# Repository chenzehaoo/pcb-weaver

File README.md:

# PCB Weaver

面向 PCB 工程的本机 MCP 与工作台：以 KiCad 为主链路，另提供独立的 Altium 静态检查内测服务。

> [!IMPORTANT]
> 项目处于开发者内测阶段。**KiCad 的样例验收不等于任意 PCB 都能自动布通；Altium 服务目前不能自动布线或回写 PCB。** 软件检查也不能替代工程师审查、打样与制造签核。

## 能力概览

| 入口 | 已实现 | 尚未覆盖 |
| --- | --- | --- |
| **KiCad 主 MCP** | 工程导入、约束布局、布线编排、原生复验、ECO、受门禁保护的制造包 | 任意复杂板的全自动完成；硬件可靠性和量产签核 |
| **Altium 内测 MCP** | 允许目录内的静态工程检查、持久任务、断线续查 | 自动布线、PCB 回写、完整 DRC、制造放行 |

## 为什么做

让 AI 参与 PCB 设计，需要让它读取真实工程、调用本机工具，并把修改结果交回设计软件检查。PCB Weaver 将这些操作组织成有版本、有任务记录、有原生证据的工程流程。

输入是**已有原理图、网络和封装的 KiCad 工程，以及结构化约束**。项目可以用于梳理工程信息、比较受约束的布局候选、提交布线与有限修复任务、检查修改结果和追踪版本变化。

## 系统架构

**图 1｜系统分层与工程域边界。** AI 客户端通过 MCP 调用工具；工作台提供本机 HTTP 入口。持久任务由工作台线程或独立 Worker 执行，KiCad 工程服务管理约束、版本和发布门禁。Altium 使用自己的 MCP、任务库与 Worker，默认仅运行静态检查。点击图片可查看矢量原图。

### KiCad 主链路如何工作

1. **导入工程**：复制工程文件与约束，记录文件哈希，建立版本快照。
2. **计算布局**：根据固定器件、区域、邻近和间距等约束生成候选，应用可行候选后创建子版本。
3. **调用布线工具**：KiCad/pcbnew 导出 DSN，Freerouting 生成 SES，再回导为待验证版本。
4. **原生复验**：运行对应版本的 ERC/DRC、网表一致性与几何等检查，保存具体失败原因和证据。
5. **显式发布**：请求制造包时重新检查，再导出真实产物、记录清单与归档哈希。

布局候选可行、布线回导成功、作业完成和制造门禁通过是不同结论。完整的[技术架构](docs/ARCHITECTURE.zh-CN.md)包含五张图，进一步说明模块分工、有限修复、版本证据、执行模型和 Altium 边界。

## 快速开始

**KiCad 主链路**（Windows PowerShell）：

```powershell
./Setup.ps1
./Start-Platform.ps1
```

需先准备 Python 3.11+。工作台默认在 `http://127.0.0.1:8765`；端口占用时运行 `./Start-Platform.ps1 -Port 8766`。`Setup.ps1` 安装项目 Python 依赖并生成本机 `.mcp.json`；原生路由仍需另行安装 KiCad、Java 和 Freerouting，并核对 `toolchain.unified.json` 的 WSL 与工具路径配置。

将 `.mcp.json` 中完整的 `pcb-weaver` 条目按客户端要求导入，启用并重载。工作台默认承载队列执行；也可以运行 `./Start-Worker.ps1` 单独执行任务。**仅连接 MCP 不会启动队列 Worker**。工作台 URL 不是 MCP stdio 地址。

完整步骤与故障排查见[部署与 MCP 接入](docs/GETTING-STARTED.zh-CN.md)。可用 `./Run-Demo.ps1` 运行小板回归，`-Route` 才会尝试完整工具链。

**Altium 静态检查内测**（单独配置）：

```powershell
./Setup-Altium-Service.ps1 -ProjectRoot 'D:\PCB-Projects'
./Start-Altium-Service.ps1
```

把生成的 `altium-local-developer-beta` 条目添加到支持 stdio 的 MCP 客户端。先调用 `altium_service_status`，再提交 `altium_submit_inspection`；任务结果用 `altium_get_job` 查询。完整安装及限制见[内测配置](docs/GITHUB-RELEASE.zh-CN.md)。

## 文档导航

| 想了解 | 文档 |
| --- | --- |
| 从安装到 MCP 调用与后台执行 | [部署与 MCP 接入](docs/GETTING-STARTED.zh-CN.md) |
| 模块、任务、版本和工程门禁 | [技术架构](docs/ARCHITECTURE.zh-CN.md) |
| Altium 工具与故障恢复 | [Altium 内测服务](docs/ALTIUM-SERVICE-BETA.zh-CN.md) |
| 本机机器接口与企业接入边界 | [集成说明](docs/INTEGRATION.zh-CN.md) |
| KiCad 实测范围与历史记录 | [固定布局验收](docs/FIXED-WHOLEBOARD-VALIDATION.md)、[系统验证](docs/SYSTEM_VALIDATION.zh-CN.md) |
| 完整文档目录与图源 | [文档导航](docs/README.md)、[架构图维护](docs/assets/architecture/README.md) |

公开仓库不包含本机工程、配置和大体积原生验收存档；克隆后必须在自己的工具链上重新验证。主项目使用 [Apache-2.0](LICENSE)，示例与第三方材料按[各自许可](THIRD_PARTY.md)使用。

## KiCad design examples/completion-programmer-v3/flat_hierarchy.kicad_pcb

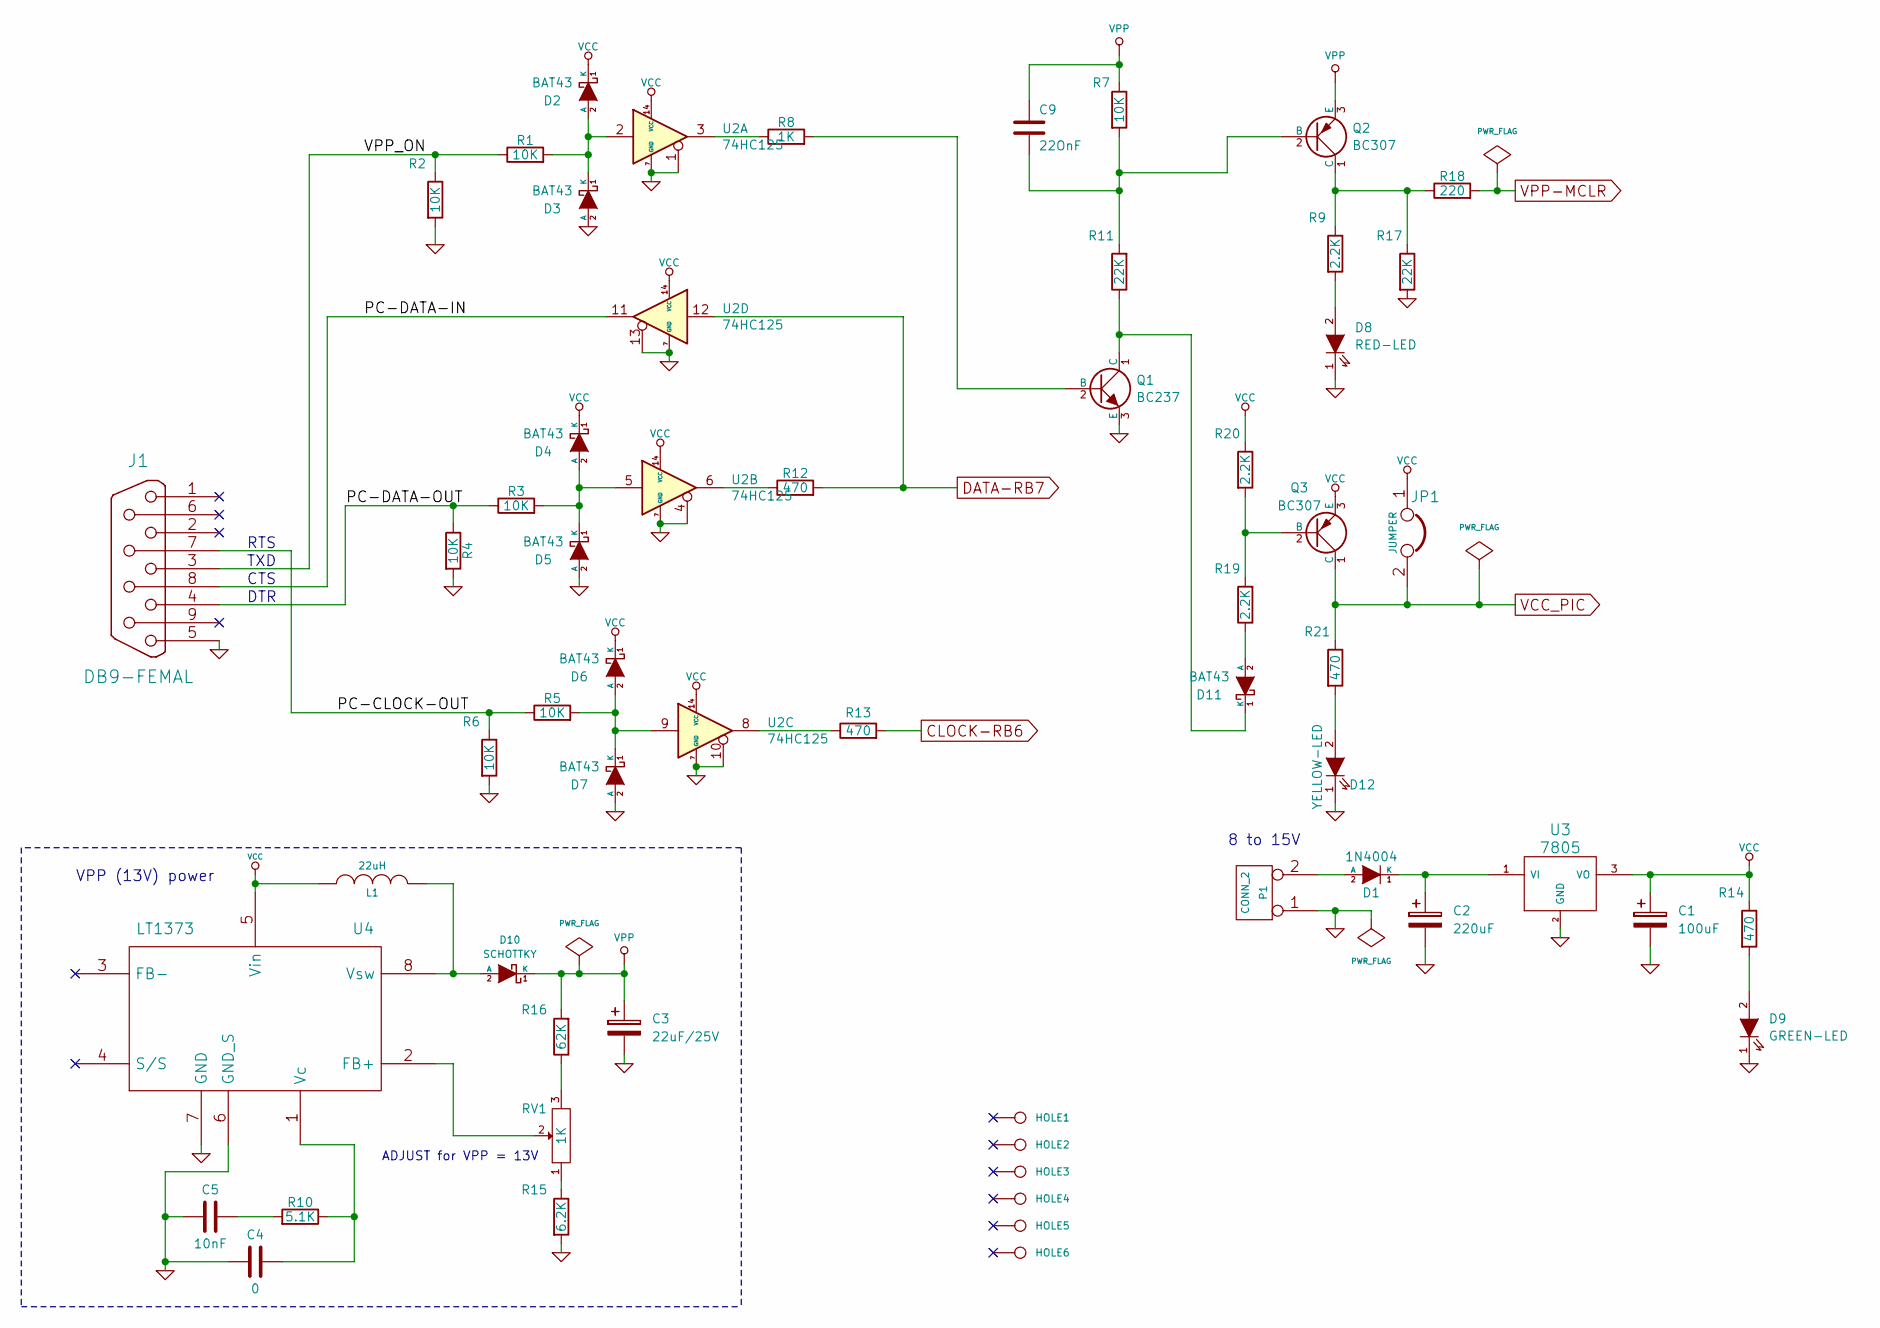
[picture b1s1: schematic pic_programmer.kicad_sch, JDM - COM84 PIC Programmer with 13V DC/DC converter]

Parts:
C1: 100uF; CP_Axial_L18.0mm_D6.5mm_P25.00mm_Horizontal
C2: 220uF; CP_Axial_L18.0mm_D6.5mm_P25.00mm_Horizontal
C3: 22uF/25V; CP_Axial_L11.0mm_D6.0mm_P18.00mm_Horizontal
C4: 0; C_Disc_D5.1mm_W3.2mm_P5.00mm
C5: 10nF; C_Disc_D5.1mm_W3.2mm_P5.00mm
C9: 22OnF; C_Disc_D5.1mm_W3.2mm_P5.00mm
D1: 1N4004; D_DO-35_SOD27_P12.70mm_Horizontal
D2, D3, D4, D5, D6, D7, D11: BAT43; D_DO-35_SOD27_P7.62mm_Horizontal
D8: RED-LED; LED_D5.0mm
D9: GREEN-LED; LED_D5.0mm
D10: SCHOTTKY; D_DO-35_SOD27_P12.70mm_Horizontal
D12: YELLOW-LED; LED_D5.0mm
HOLE1, HOLE2, HOLE3, HOLE4, HOLE5, HOLE6: P***; MountingHole_4.3mm_M4_DIN965
J1: DB9-FEMAL; DSUB-9_Female_Horizontal_P2.77x2.84mm_EdgePinOffset7.70mm_H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
JP1: JUMPER; PinHeader_1x02_P2.54mm_Vertical
L1: 22uH; INDUCTOR_V
P1: CONN_2; Altech_AK300_1x02_P5.00mm_45-Degree
Q1: BC237; TO-92
Q2, Q3: BC307; TO-92
R1, R2, R3, R4, R5, R6, R7: 10K; R_Axial_DIN0207_L6.3mm_D2.5mm_P10.16mm_Horizontal
R8: 1K; R_Axial_DIN0207_L6.3mm_D2.5mm_P10.16mm_Horizontal
R9, R19, R20: 2.2K; R_Axial_DIN0207_L6.3mm_D2.5mm_P10.16mm_Horizontal
R10: 5.1K; R_Axial_DIN0207_L6.3mm_D2.5mm_P10.16mm_Horizontal
R11, R17: 22K; R_Axial_DIN0207_L6.3mm_D2.5mm_P10.16mm_Horizontal
R12, R13, R14, R21: 470; R_Axial_DIN0207_L6.3mm_D2.5mm_P10.16mm_Horizontal
R15: 6.2K; R_Axial_DIN0207_L6.3mm_D2.5mm_P10.16mm_Horizontal
R16: 62K; R_Axial_DIN0207_L6.3mm_D2.5mm_P10.16mm_Horizontal
R18: 220; R_Axial_DIN0207_L6.3mm_D2.5mm_P10.16mm_Horizontal
RV1: 1K; RV2X4
U2: 74HC125; DIP-14_W7.62mm_LongPads
U3: 7805; TO-220-3_Horizontal_TabDown
U4: LT1373; DIP-8_W7.62mm_LongPads

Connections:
/pic_programmer/PC-CLOCK-OUT: J1.7, R5.1, R6.1
/pic_programmer/PC-DATA-IN: J1.8, U2.11
/pic_programmer/PC-DATA-OUT: J1.4, R3.1, R4.1
/pic_programmer/VPP_ON: J1.3, R1.1, R2.1
CLOCK-RB6: R13.2; also elsewhere on the board
DATA-RB7: R12.2, U2.12; also elsewhere on the board
GND: C1.2, C2.2, C3.2, C4.2, C5.2, D3.2 (A), D5.2 (A), D7.2 (A), D8.1 (K), D9.1 (K), D12.1 (K), J1.5, P1.1, Q1.3 (E), R2.2, R4.2, R6.2, R15.2, R17.2, U2.1, U2.4, U2.7 (GND), U2.10, U2.13, U3.2 (GND), U4.6 (GND_S), U4.7 (GND); also elsewhere on the board
unnamed: C5.1, R10.2
unnamed: D1.2 (A), P1.2 (PM)
unnamed: C2.1, D1.1 (K), U3.1 (VI)
unnamed: D2.2 (A), D3.1 (K), R1.2, U2.2
unnamed: D4.2 (A), D5.1 (K), R3.2, U2.5
unnamed: D6.2 (A), D7.1 (K), R5.2, U2.9
unnamed: D8.2 (A), R9.2
unnamed: D9.2 (A), R14.2
unnamed: D10.2 (A), L1.1, U4.8 (Vsw)
unnamed: D11.2 (A), R19.1
unnamed: D11.1 (K), Q1.1 (C), R11.1
unnamed: D12.2 (A), R21.2
unnamed: Q1.2 (B), R8.2
unnamed: C9.2, Q2.2 (B), R7.2, R11.2
unnamed: Q2.1 (C), R9.1, R17.1, R18.1
unnamed: Q3.2 (B), R19.2, R20.2
unnamed: R8.1, U2.3
unnamed: R12.1, U2.6
unnamed: R13.1, U2.8
unnamed: R15.1, RV1.1
unnamed: R16.1, RV1.3
unnamed: RV1.2, U4.2 (FB+)
unnamed: C4.1, R10.1, U4.1 (Vc)
VCC: C1.1, D2.1 (K), D4.1 (K), D6.1 (K), JP1.1, L1.2, Q3.3 (E), R14.1, R20.1, U2.14 (VCC), U3.3 (VO), U4.5 (Vin); also elsewhere on the board
VCC_PIC: JP1.2, Q3.1 (C), R21.1; also elsewhere on the board
VPP: C3.1, C9.1, D10.1 (K), Q2.3 (E), R7.1, R16.2
VPP-MCLR: R18.2; also elsewhere on the board

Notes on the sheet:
TXD
CTS
DTR
VPP (13V) power
ADJUST for VPP = 13V
RTS
8 to 15V

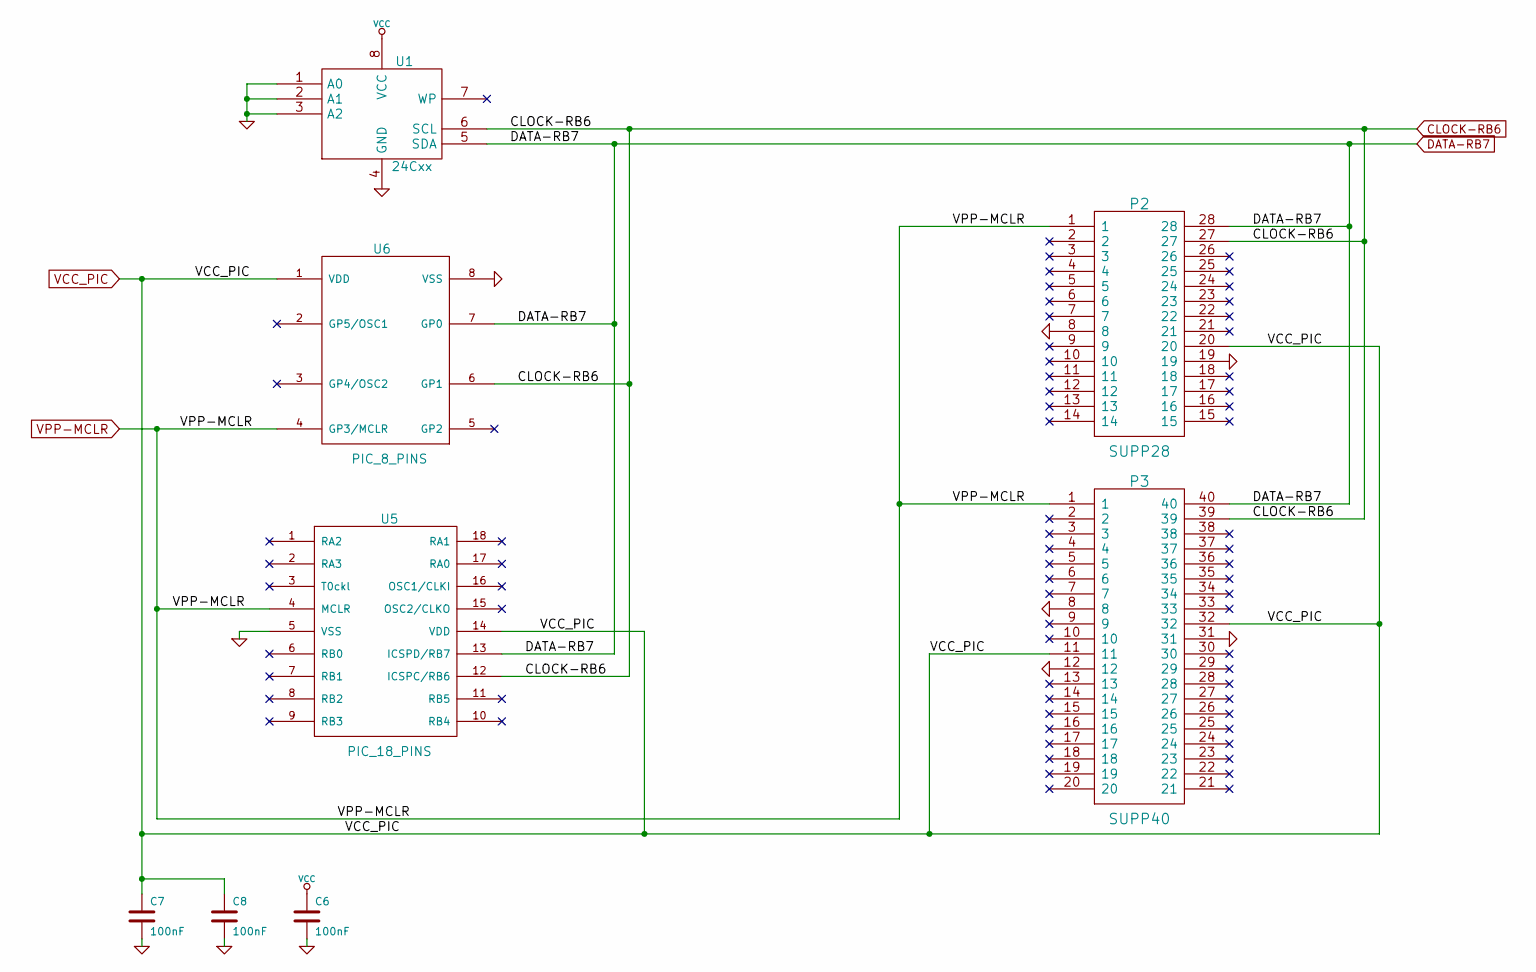
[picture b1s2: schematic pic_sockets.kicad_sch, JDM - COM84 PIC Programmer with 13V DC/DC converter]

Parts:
C6, C7, C8: 100nF; C_Disc_D5.1mm_W3.2mm_P5.00mm
P2: SUPP28; DIP-28_W7.62mm_Socket_LongPads
P3: SUPP40; DIP-40_W15.24mm_Socket_LongPads
U1: 24Cxx; DIP-8_W7.62mm_LongPads
U5: PIC_18_PINS; DIP-18_W7.62mm_Socket_LongPads
U6: PIC_8_PINS; DIP-8_W7.62mm_LongPads

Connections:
CLOCK-RB6: P2.27, P3.39, U1.6 (SCL), U5.12 (ICSPC/RB6), U6.6 (GP1); also elsewhere on the board
DATA-RB7: P2.28, P3.40, U1.5 (SDA), U5.13 (ICSPD/RB7), U6.7 (GP0); also elsewhere on the board
GND: C6.2, C7.2, C8.2, P2.8, P2.19, P3.8, P3.12, P3.31, U1.1 (A0), U1.2 (A1), U1.3 (A2), U1.4 (GND), U5.5 (VSS), U6.8 (VSS); also elsewhere on the board
VCC: C6.1, U1.8 (VCC); also elsewhere on the board
VCC_PIC: C7.1, C8.1, P2.20, P3.11, P3.32, U5.14 (VDD), U6.1 (VDD); also elsewhere on the board
VPP-MCLR: P2.1, P3.1, U5.4 (MCLR), U6.4 (GP3/MCLR); also elsewhere on the board

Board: 2 copper layers, 64 parts (0 on the bottom side), 34 nets, no tracks yet.

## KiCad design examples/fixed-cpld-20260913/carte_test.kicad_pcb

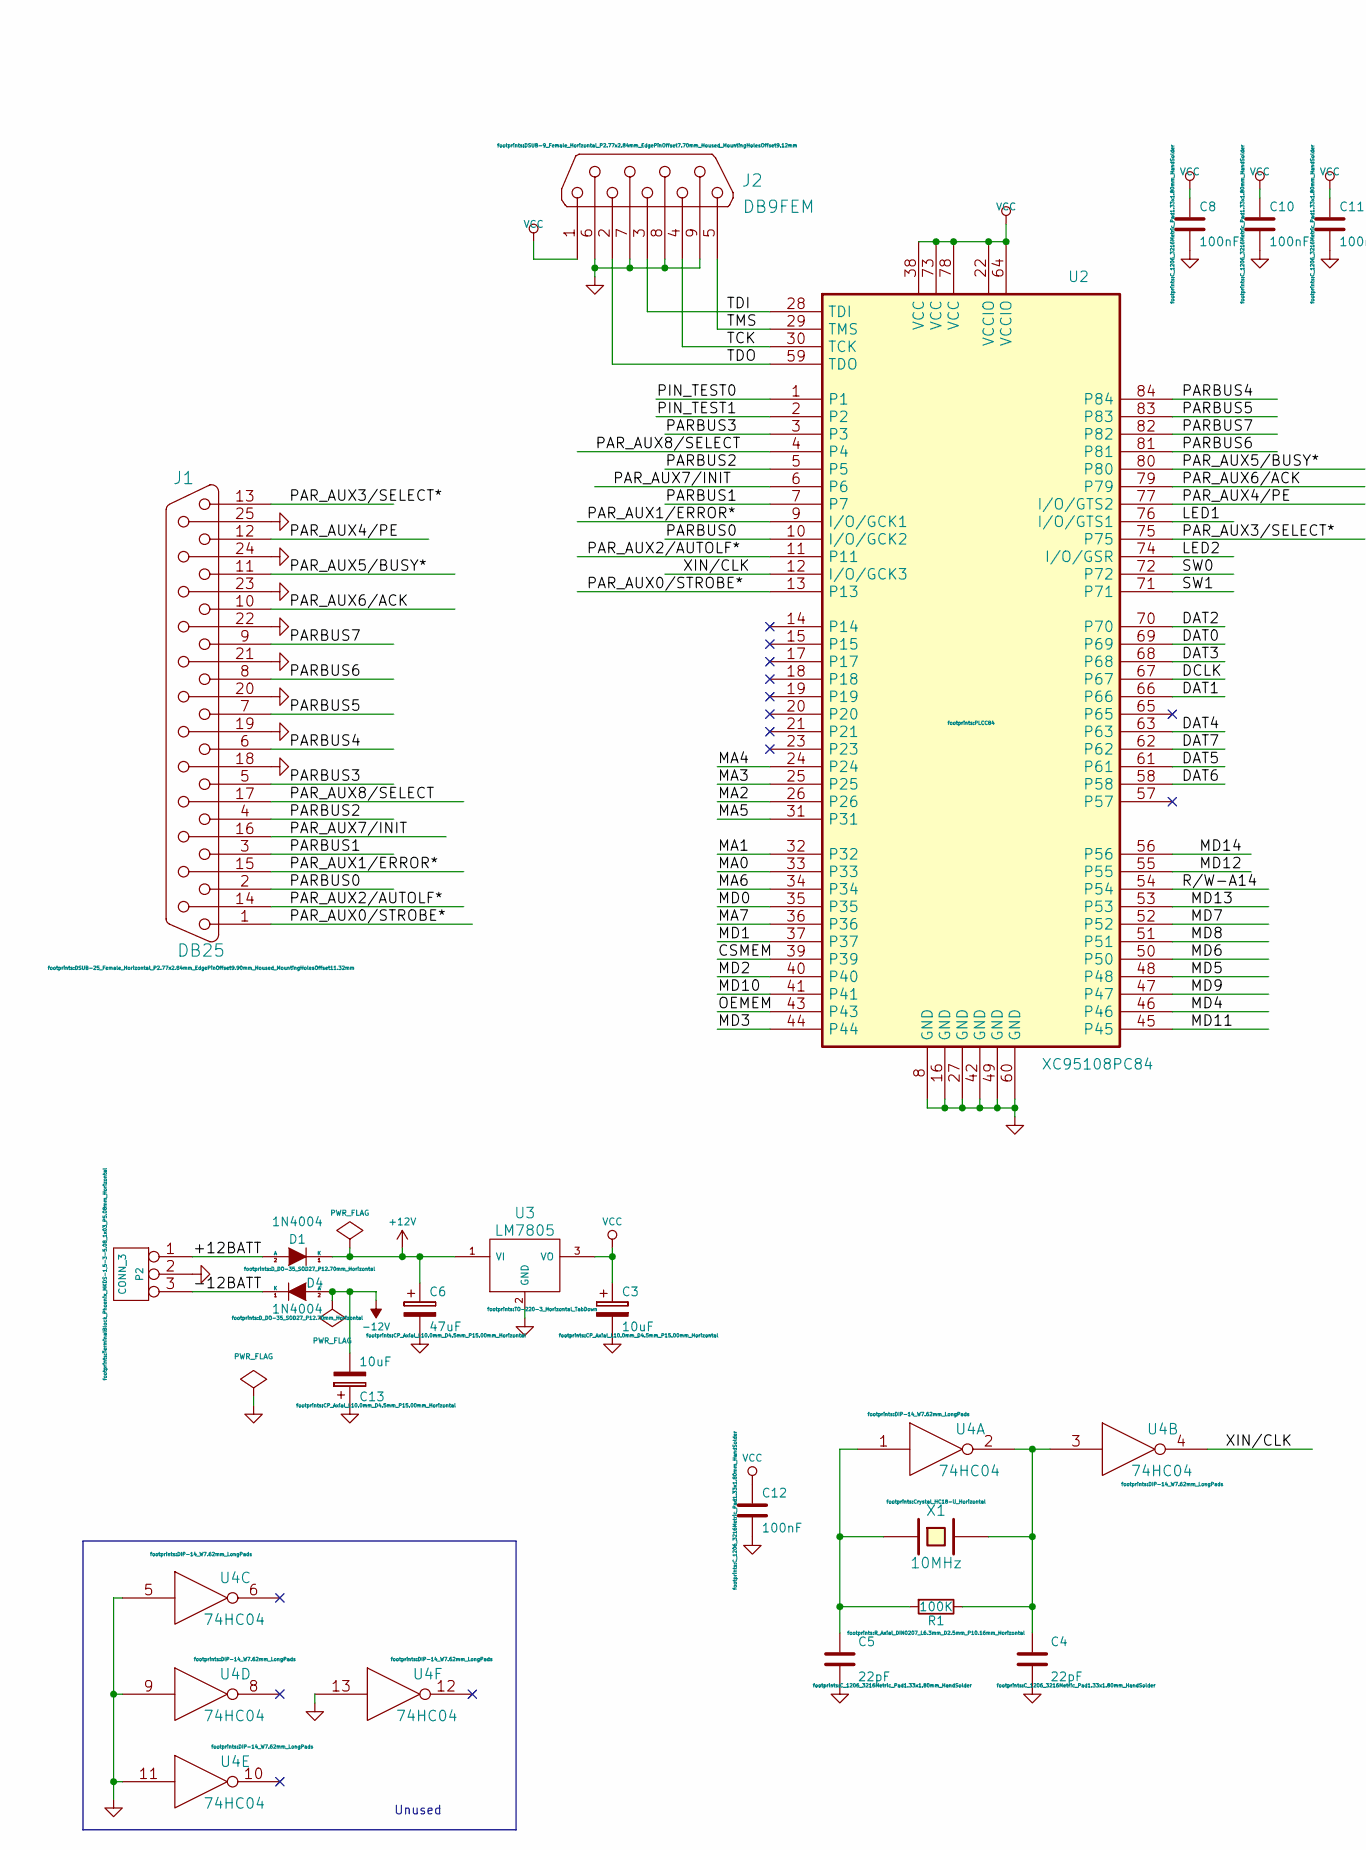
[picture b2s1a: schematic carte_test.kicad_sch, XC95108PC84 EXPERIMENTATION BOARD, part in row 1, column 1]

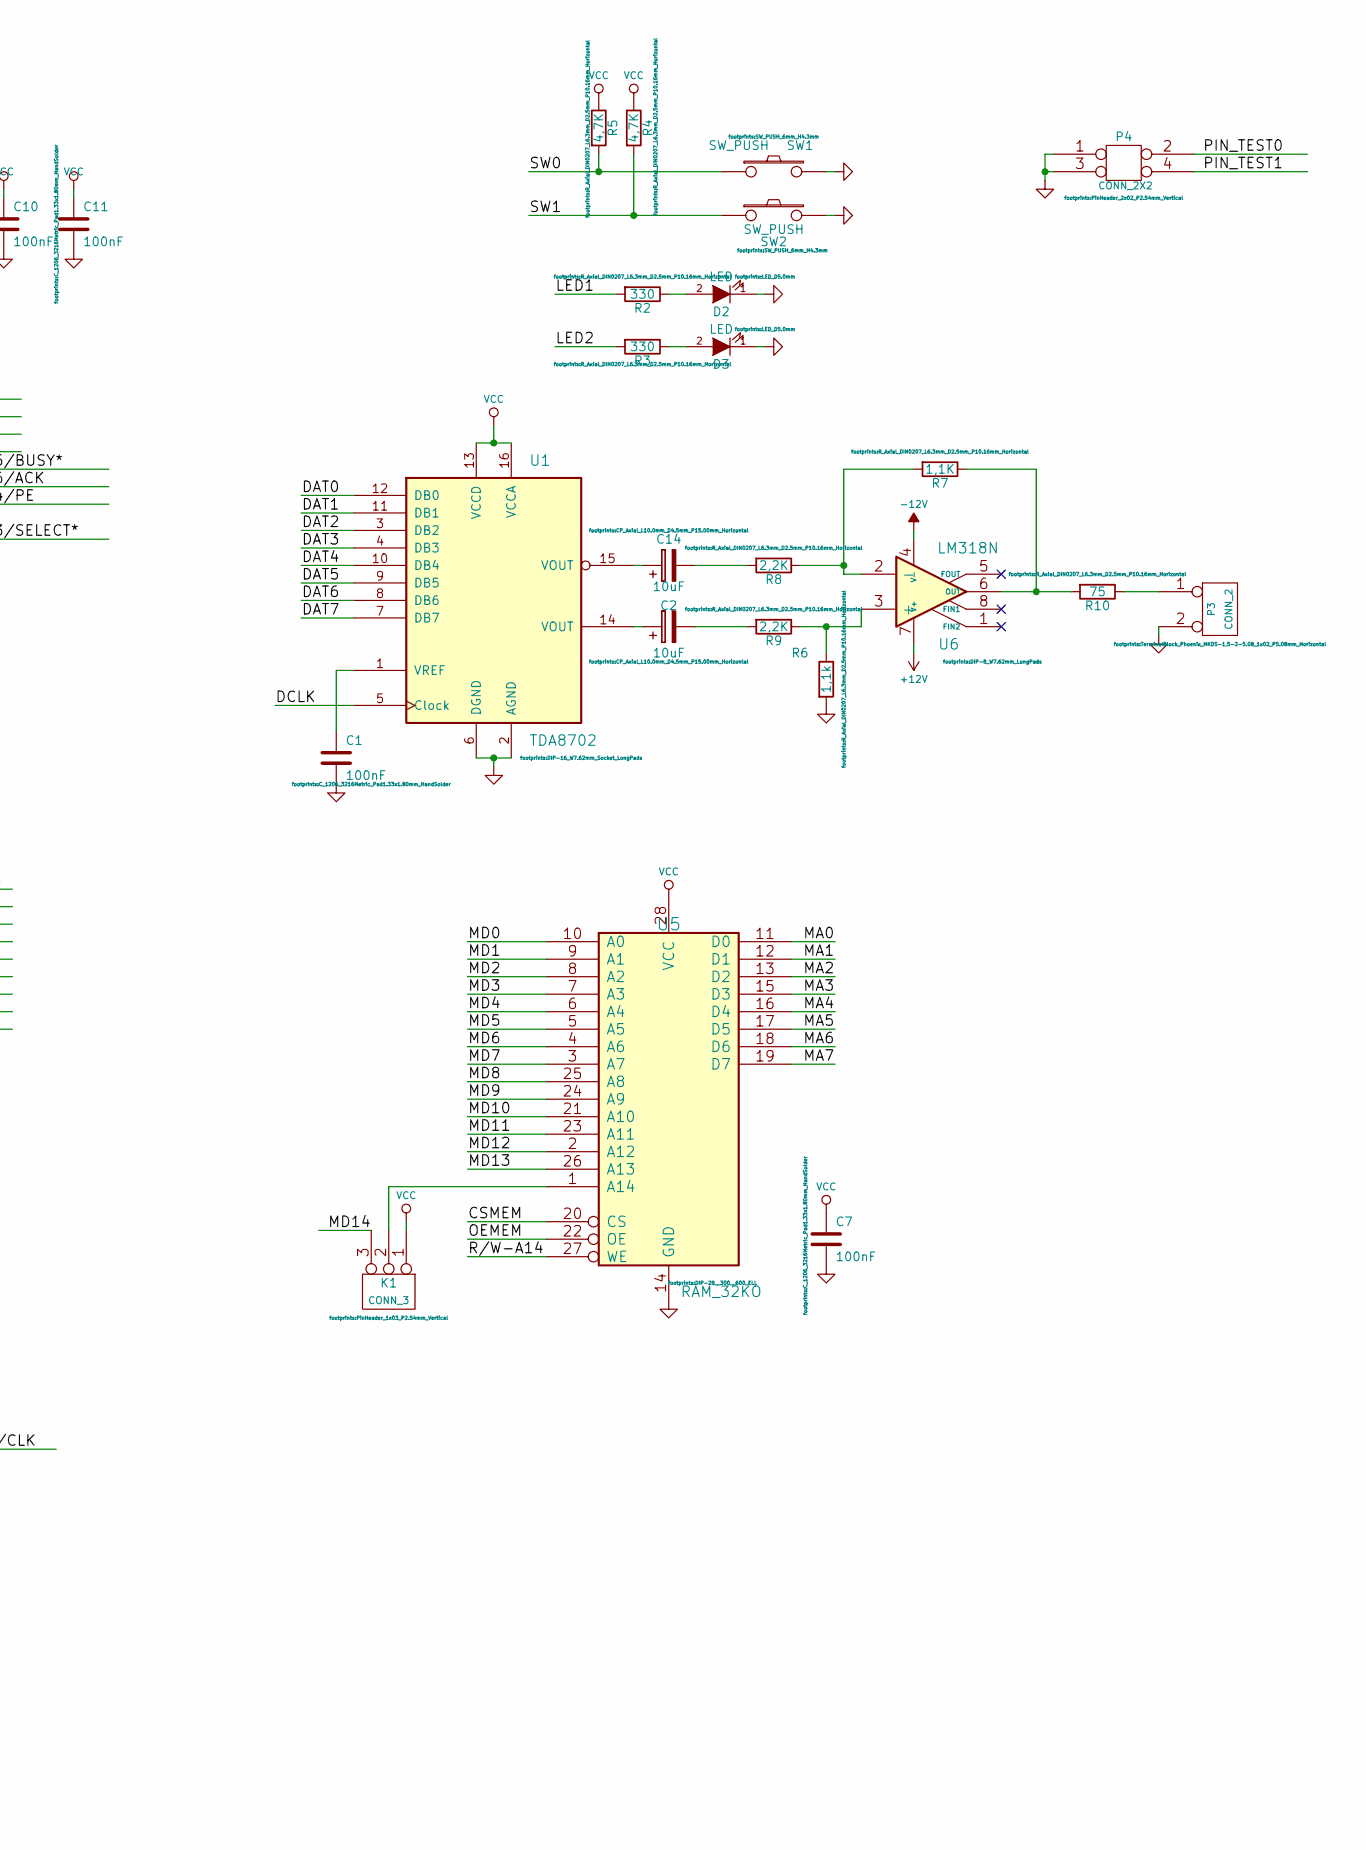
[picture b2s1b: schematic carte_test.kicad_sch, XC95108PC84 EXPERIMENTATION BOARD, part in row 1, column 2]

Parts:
C1, C7, C8, C10, C11, C12: 100nF; C_1206_3216Metric_Pad1.33x1.80mm_HandSolder
C2, C3, C13, C14: 10uF; CP_Axial_L10.0mm_D4.5mm_P15.00mm_Horizontal
C4, C5: 22pF; C_1206_3216Metric_Pad1.33x1.80mm_HandSolder
C6: 47uF; CP_Axial_L10.0mm_D4.5mm_P15.00mm_Horizontal
D1, D4: 1N4004; D_DO-35_SOD27_P12.70mm_Horizontal
D2, D3: LED; LED_D5.0mm
J1: DB25; DSUB-25_Female_Horizontal_P2.77x2.84mm_EdgePinOffset9.90mm_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
J2: DB9FEM; DSUB-9_Female_Horizontal_P2.77x2.84mm_EdgePinOffset7.70mm_H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
K1: CONN_3; PinHeader_1x03_P2.54mm_Vertical
P2: CONN_3; TerminalBlock_Phoenix_MKDS-1,5-3-5.08_1x03_P5.08mm_Horizont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
P3: CONN_2; TerminalBlock_Phoenix_MKDS-1,5-2-5.08_1x02_P5.08mm_Horizont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
P4: CONN_2X2; PinHeader_2x02_P2.54mm_Vertical
R1: 100K; R_Axial_DIN0207_L6.3mm_D2.5mm_P10.16mm_Horizontal
R2, R3: 330; R_Axial_DIN0207_L6.3mm_D2.5mm_P10.16mm_Horizontal
R4, R5: 4,7K; R_Axial_DIN0207_L6.3mm_D2.5mm_P10.16mm_Horizontal
R6: 1,1k; R_Axial_DIN0207_L6.3mm_D2.5mm_P10.16mm_Horizontal
R7: 1,1K; R_Axial_DIN0207_L6.3mm_D2.5mm_P10.16mm_Horizontal
R8, R9: 2,2K; R_Axial_DIN0207_L6.3mm_D2.5mm_P10.16mm_Horizontal
R10: 75; R_Axial_DIN0207_L6.3mm_D2.5mm_P10.16mm_Horizontal
SW1, SW2: SW_PUSH; SW_PUSH_6mm_H4.3mm
U1: TDA8702; DIP-16_W7.62mm_Socket_LongPads
U2: XC95108PC84; PLCC84
U3: LM7805; TO-220-3_Horizontal_TabDown
U4: 74HC04; DIP-14_W7.62mm_LongPads
U5: RAM_32KO; DIP-28__300__600_ELL
U6: LM318N; DIP-8_W7.62mm_LongPads
X1: 10MHz; Crystal_HC18-U_Horizontal

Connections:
+12V: C6.1, D1.1 (K), U3.1 (VI), U6.7 (V+)
-12V: C13.2, D4.2 (A), U6.4 (V-)
/+12BATT: D1.2 (A), P2.1
/-12BATT: D4.1 (K), P2.3
/CSMEM: U2.39, U5.20 (CS)
/DAT0: U1.12 (DB0), U2.69
/DAT1: U1.11 (DB1), U2.66
/DAT2: U1.3 (DB2), U2.70
/DAT3: U1.4 (DB3), U2.68
/DAT4: U1.10 (DB4), U2.63
/DAT5: U1.9 (DB5), U2.61
/DAT6: U1.8 (DB6), U2.58
/DAT7: U1.7 (DB7), U2.62
/DCLK: U1.5 (Clock), U2.67
/LED1: R2.2, U2.76 (I/O/GTS1)
/LED2: R3.2, U2.74 (I/O/GSR)
/MA0: U2.33, U5.11 (D0)
/MA1: U2.32, U5.12 (D1)
/MA2: U2.26, U5.13 (D2)
/MA3: U2.25, U5.15 (D3)
/MA4: U2.24, U5.16 (D4)
/MA5: U2.31, U5.17 (D5)
/MA6: U2.34, U5.18 (D6)
/MA7: U2.36, U5.19 (D7)
/MD0: U2.35, U5.10 (A0)
/MD1: U2.37, U5.9 (A1)
/MD2: U2.40, U5.8 (A2)
/MD3: U2.44, U5.7 (A3)
/MD4: U2.46, U5.6 (A4)
/MD5: U2.48, U5.5 (A5)
/MD6: U2.50, U5.4 (A6)
/MD7: U2.52, U5.3 (A7)
/MD8: U2.51, U5.25 (A8)
/MD9: U2.47, U5.24 (A9)
/MD10: U2.41, U5.21 (A10)
/MD11: U2.45, U5.23 (A11)
/MD12: U2.55, U5.2 (A12)
/MD13: U2.53, U5.26 (A13)
/MD14: K1.3, U2.56
/OEMEM: U2.43, U5.22 (OE)
/PARBUS0: J1.2, U2.10 (I/O/GCK2)
/PARBUS1: J1.3, U2.7
/PARBUS2: J1.4, U2.5
/PARBUS3: J1.5, U2.3
/PARBUS4: J1.6, U2.84
/PARBUS5: J1.7, U2.83
/PARBUS6: J1.8, U2.81
/PARBUS7: J1.9, U2.82
/PAR_AUX0/STROBE*: J1.1, U2.13
/PAR_AUX1/ERROR*: J1.15, U2.9 (I/O/GCK1)
/PAR_AUX2/AUTOLF*: J1.14, U2.11
/PAR_AUX3/SELECT*: J1.13, U2.75
/PAR_AUX4/PE: J1.12, U2.77 (I/O/GTS2)
/PAR_AUX5/BUSY*: J1.11, U2.80
/PAR_AUX6/ACK: J1.10, U2.79
/PAR_AUX7/INIT: J1.16, U2.6
/PAR_AUX8/SELECT: J1.17, U2.4
/PIN_TEST0: P4.2, U2.1
/PIN_TEST1: P4.4, U2.2
/R/W-A14: U2.54, U5.27 (WE)
/SW0: R5.2, SW1.1, U2.72
/SW1: R4.2, SW2.1, U2.71
/TCK: J2.4, U2.30 (TCK)
/TDI: J2.3, U2.28 (TDI)
/TDO: J2.2, U2.59 (TDO)
/TMS: J2.5, U2.29 (TMS)
/XIN/CLK: U2.12 (I/O/GCK3), U4.4
GND: C1.2, C3.2, C4.2, C5.2, C6.2, C7.2, C8.2, C10.2, C11.2, C12.2, C13.1, D2.1 (K), D3.1 (K), J1.18, J1.19, J1.20, J1.21, J1.22, J1.23, J1.24, J1.25, J2.6, J2.7, J2.8, J2.9, P2.2 (PM), P3.2 (PM), P4.1, P4.3, R6.2, SW1.2, SW2.2, U1.2 (AGND), U1.6 (DGND), U2.8 (GND), U2.16 (GND), U2.27 (GND), U2.42 (GND), U2.49 (GND), U2.60 (GND), U3.2 (GND), U4.5, U4.7 (GND), U4.9, U4.11, U4.13, U5.14 (GND)
unnamed: C2.1, U1.14 (VOUT)
unnamed: C2.2, R9.2
unnamed: C4.1, R1.1, U4.2, U4.3, X1.2
unnamed: C5.1, R1.2, U4.1, X1.1
unnamed: C14.1, U1.15 (VOUT)
unnamed: C14.2, R8.2
unnamed: D2.2 (A), R2.1
unnamed: D3.2 (A), R3.1
unnamed: K1.2 (PM), U5.1 (A14)
unnamed: P3.1, R10.1
unnamed: C1.1, U1.1 (VREF)
unnamed: R6.1, R9.1, U6.3 (+)
unnamed: R7.2, R8.1, U6.2 (-)
unnamed: R7.1, R10.2, U6.6 (OUT)
VCC: C3.1, C7.1, C8.1, C10.1, C11.1, C12.1, J2.1, K1.1, R4.1, R5.1, U1.13 (VCCD), U1.16 (VCCA), U2.22 (VCCIO), U2.38 (VCC), U2.64 (VCCIO), U2.73 (VCC), U2.78 (VCC), U3.3 (VO), U4.14 (VCC), U5.28 (VCC)

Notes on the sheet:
Unused

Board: 2 copper layers, 42 parts (8 on the bottom side), 83 nets, no tracks yet.

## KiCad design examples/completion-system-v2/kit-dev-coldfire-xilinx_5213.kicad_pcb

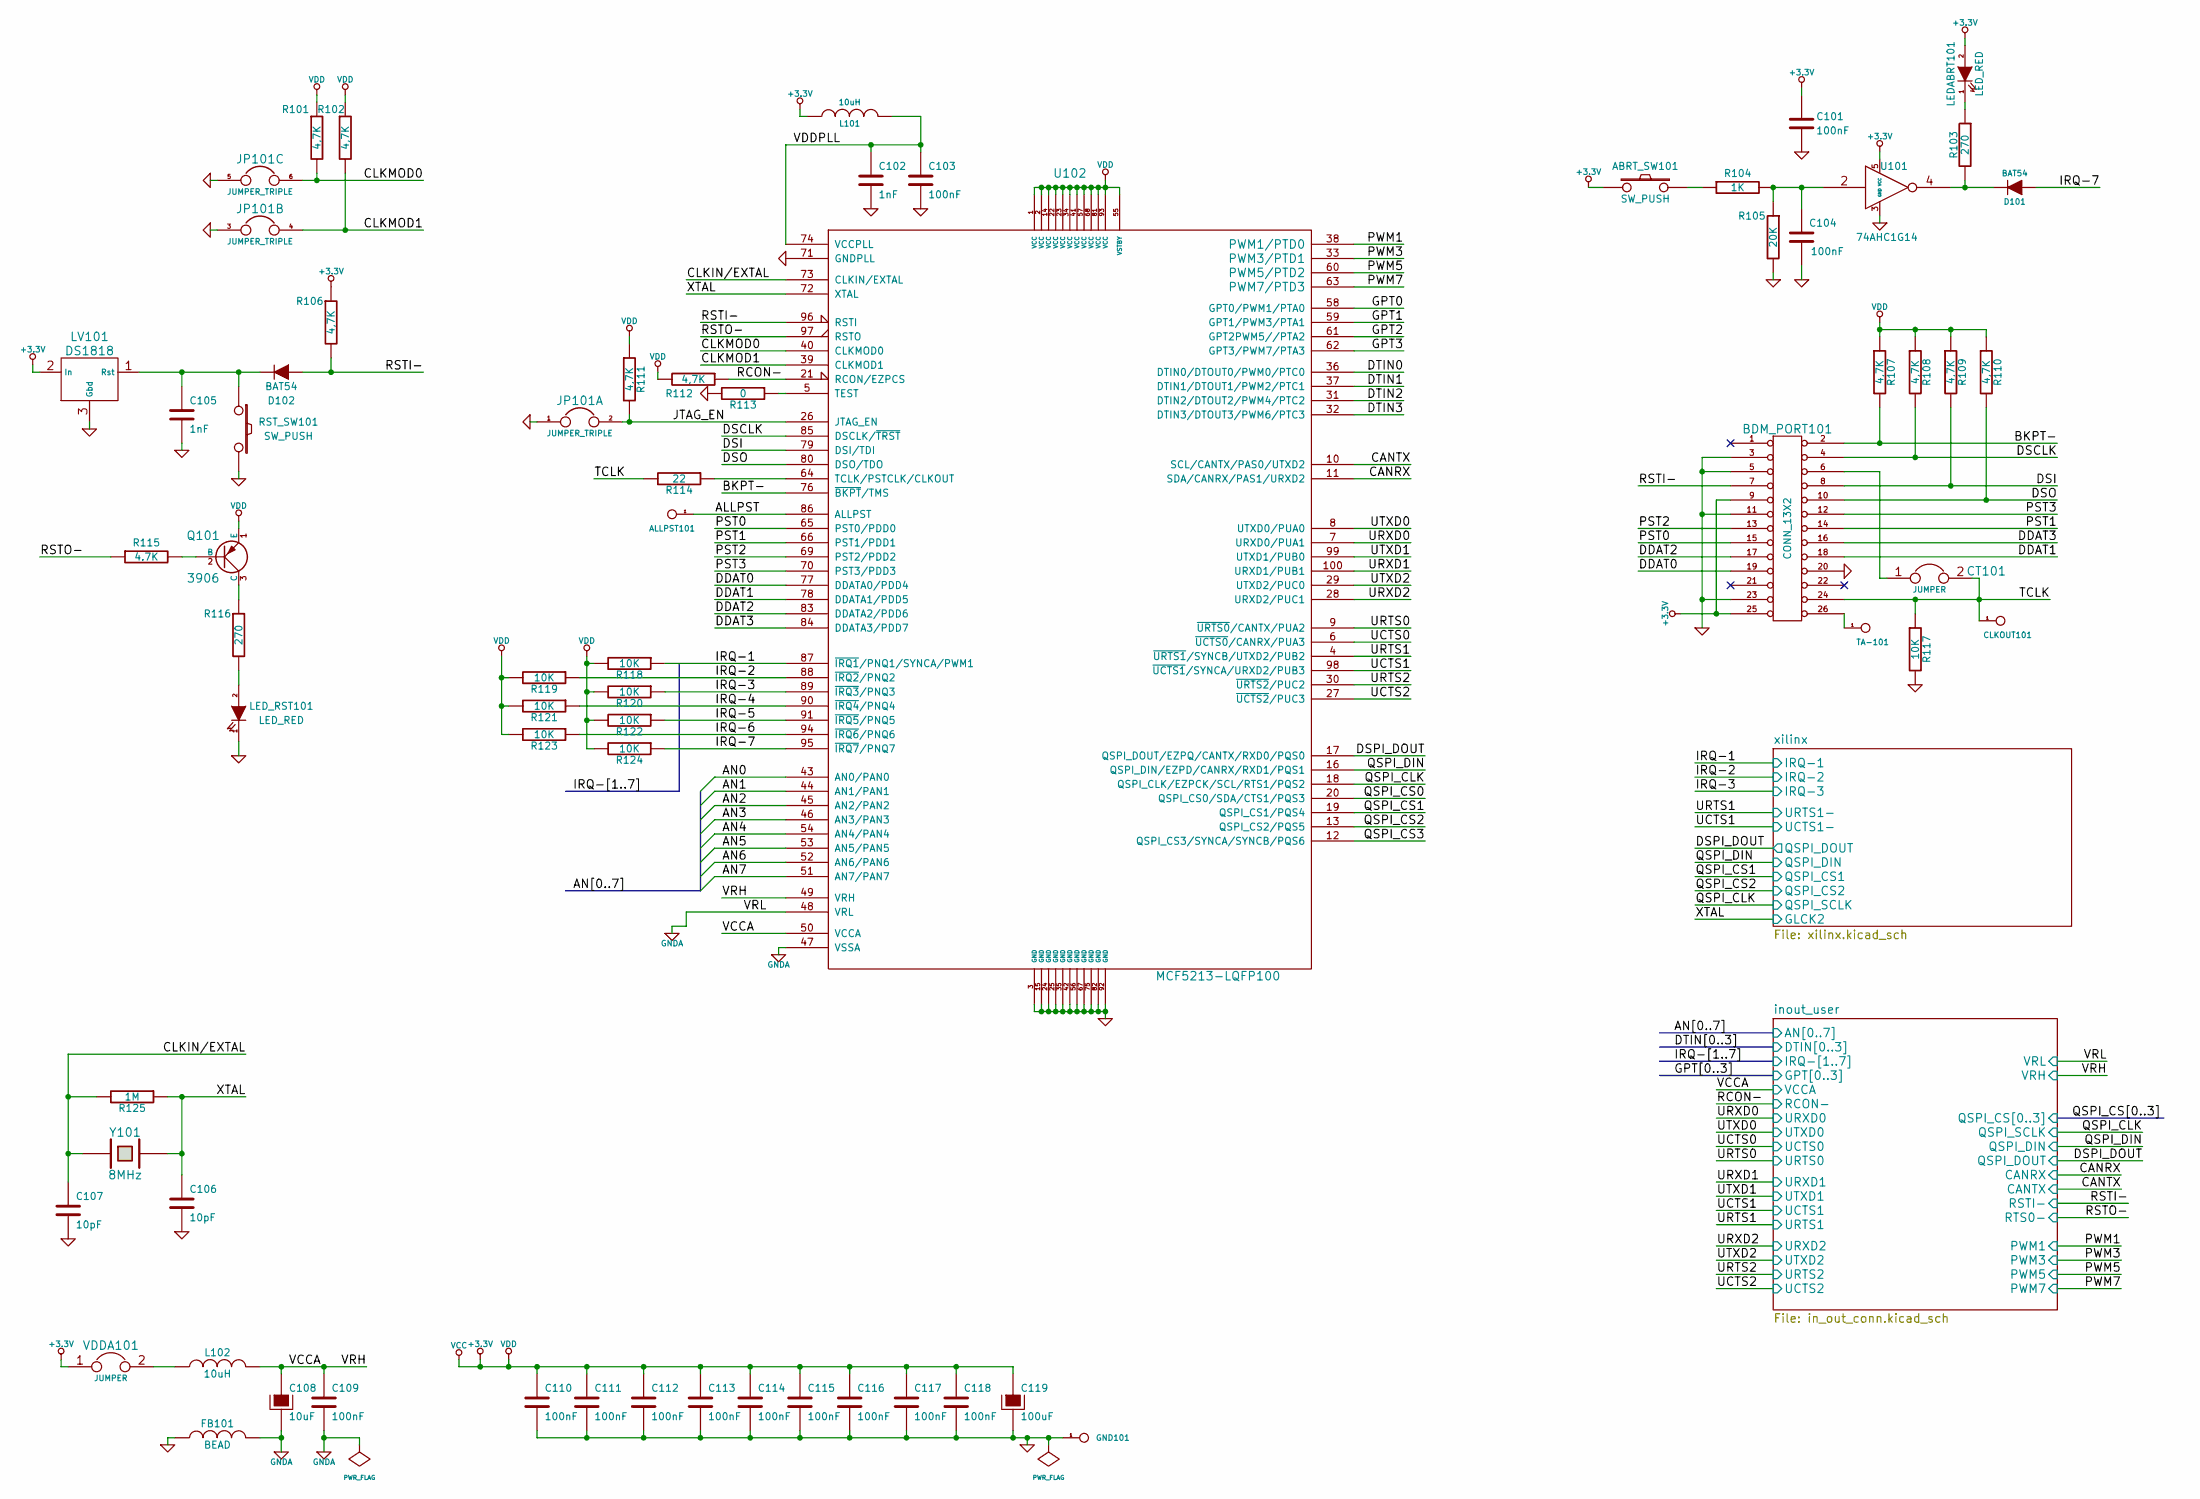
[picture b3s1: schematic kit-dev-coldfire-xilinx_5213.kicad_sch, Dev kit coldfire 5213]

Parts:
ABRT_SW101: SW_PUSH; SW_PUSH_SMALL
ALLPST101: CONN_1; PinHeader_1x01_P2.54mm_Vertical
BDM_PORT101: CONN_13X2; PinHeader_2x13_P2.54mm_Vertical
C101, C103, C104, C109, C110, C111, C112, C113, C114, C115, C116, C117, C118: 100nF; C_0805_2012Metric
C102, C105: 1nF; C_0805_2012Metric
C106, C107: 10pF; C_0805_2012Metric
C108: 10uF; SM1206POL
C119: 100uF; SM1206POL
CLKOUT101: CONN_1; PinHeader_1x01_P2.54mm_Vertical
CT101: JUMPER; PinHeader_1x02_P2.54mm_Vertical
D101, D102: BAT54; D_SOT-23_ANK
FB101: BEAD; R_1206_3216Metric_Pad1.30x1.75mm_HandSolder
GND101: CONN_1; PinHeader_1x01_P2.54mm_Vertical
JP101: JUMPER_TRIPLE; PinHeader_2x03_P2.54mm_Vertical
L101, L102: 10uH; R_1206_3216Metric_Pad1.30x1.75mm_HandSolder
LEDABRT101: LED_RED; LED_1206_3216Metric
LED_RST101: LED_RED; LED_1206_3216Metric
LV101: DS1818; TO-92
Q101: 3906; SOT23EBC
R101, R102, R106, R107, R108, R109, R110, R111, R112: 4,7K; R_0805_2012Metric
R103, R116: 270; R_0805_2012Metric
R104: 1K; R_0805_2012Metric
R105: 20K; R_0805_2012Metric
R113: 0; R_0805_2012Metric
R114: 22; R_0805_2012Metric
R115: 4.7K; R_0805_2012Metric
R117, R118, R119, R120, R121, R122, R123, R124: 10K; R_0805_2012Metric
R125: 1M; R_0805_2012Metric
RST_SW101: SW_PUSH; SW_PUSH_SMALL
TA-101: CONN_1; PinHeader_1x01_P2.54mm_Vertical
U101: 74AHC1G14; SOT353
U102: MCF5213-LQFP100; LQFP-100_14x14mm_P0.5mm
VDDA101: JUMPER; PinHeader_1x02_P2.54mm_Vertical
Y101: 8MHz; Crystal_HC18-U_Horizontal

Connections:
+3.3V: ABRT_SW101.2, BDM_PORT101.9, BDM_PORT101.25 (P24), C101.2, C110.1, C111.1, C112.1, C113.1, C114.1, C115.1, C116.1, C117.1, C118.1, C119.1, L101.1, LEDABRT101.2 (A), LV101.2 (In), Q101.1 (E), R101.1, R102.1, R106.1, R107.1, R108.1, R109.1, R110.1, R111.1, R112.2, R118.2, R119.2, R120.2, R121.2, R122.2, R123.2, R124.2, U101.5 (VCC), U102.1 (VCC), U102.2 (VCC), U102.14 (VCC), U102.22 (VCC), U102.23 (VCC), U102.34 (VCC), U102.41 (VCC), U102.55 (VSTBY), U102.57 (VCC), U102.68 (VCC), U102.81 (VCC), U102.93 (VCC), VDDA101.1; also elsewhere on the board
/ALLPST: ALLPST101.1, U102.86 (ALLPST)
/AN0: U102.43 (AN0/PAN0); also elsewhere on the board
/AN1: U102.44 (AN1/PAN1); also elsewhere on the board
/AN2: U102.45 (AN2/PAN2); also elsewhere on the board
/AN3: U102.46 (AN3/PAN3); also elsewhere on the board
/AN4: U102.54 (AN4/PAN4); also elsewhere on the board
/AN5: U102.53 (AN5/PAN5); also elsewhere on the board
/AN6: U102.52 (AN6/PAN6); also elsewhere on the board
/AN7: U102.51 (AN7/PAN7); also elsewhere on the board
/BKPT-: BDM_PORT101.2, R107.2, U102.76 (~BKPT/TMS)
/CANRX: U102.11 (SDA/CANRX/PAS1/URXD2); also elsewhere on the board
/CANTX: U102.10 (SCL/CANTX/PAS0/UTXD2); also elsewhere on the board
/CLKIN/EXTAL: C107.1, R125.2, U102.73 (CLKIN/EXTAL), Y101.1
/CLKMOD0: JP101.6, R101.2, U102.40 (CLKMOD0)
/CLKMOD1: JP101.4, R102.2, U102.39 (CLKMOD1)
/DDAT0: BDM_PORT101.19, U102.77 (DDATA0/PDD4)
/DDAT1: BDM_PORT101.18, U102.78 (DDATA1/PDD5)
/DDAT2: BDM_PORT101.17, U102.83 (DDATA2/PDD6)
/DDAT3: BDM_PORT101.16, U102.84 (DDATA3/PDD7)
/DSCLK: BDM_PORT101.4, R108.2, U102.85 (DSCLK/~TRST)
/DSI: BDM_PORT101.8, R109.2, U102.79 (DSI/TDI)
/DSO: BDM_PORT101.10, R110.2, U102.80 (DSO/TDO)
/DSPI_DOUT: U102.17 (QSPI_DOUT/EZPQ/CANTX/RXD0/PQS0); also elsewhere on the board
/DTIN0: U102.36 (DTIN0/DTOUT0/PWM0/PTC0); also elsewhere on the board
/DTIN1: U102.37 (DTIN1/DTOUT1/PWM2/PTC1); also elsewhere on the board
/DTIN2: U102.31 (DTIN2/DTOUT2/PWM4/PTC2); also elsewhere on the board
/DTIN3: U102.32 (DTIN3/DTOUT3/PWM6/PTC3); also elsewhere on the board
/GPT0: U102.58 (GPT0/PWM1/PTA0); also elsewhere on the board
/GPT1: U102.59 (GPT1/PWM3/PTA1); also elsewhere on the board
/GPT2: U102.61 (GPT2PWM5//PTA2); also elsewhere on the board
/GPT3: U102.62 (GPT3/PWM7/PTA3); also elsewhere on the board
/IRQ-1: R118.1, U102.87 (~IRQ1/PNQ1/SYNCA/PWM1); also elsewhere on the board
/IRQ-2: R119.1, U102.88 (~IRQ2/PNQ2); also elsewhere on the board
/IRQ-3: R120.1, U102.89 (~IRQ3/PNQ3); also elsewhere on the board
/IRQ-4: R121.1, U102.90 (~IRQ4/PNQ4); also elsewhere on the board
/IRQ-5: R122.1, U102.91 (~IRQ5/PNQ5); also elsewhere on the board
/IRQ-6: R123.1, U102.94 (~IRQ6/PNQ6); also elsewhere on the board
/IRQ-7: D101.2 (A), R124.1, U102.95 (~IRQ7/PNQ7); also elsewhere on the board
/JTAG_EN: JP101.2, R111.2, U102.26 (JTAG_EN)
/PST0: BDM_PORT101.15, U102.65 (PST0/PDD0)
/PST1: BDM_PORT101.14, U102.66 (PST1/PDD1)
/PST2: BDM_PORT101.13, U102.69 (PST2/PDD2)
/PST3: BDM_PORT101.12, U102.70 (PST3/PDD3)
/PWM1: U102.38 (PWM1/PTD0); also elsewhere on the board
/PWM3: U102.33 (PWM3/PTD1); also elsewhere on the board
/PWM5: U102.60 (PWM5/PTD2); also elsewhere on the board
/PWM7: U102.63 (PWM7/PTD3); also elsewhere on the board
/QSPI_CLK: U102.18 (QSPI_CLK/EZPCK/SCL/RTS1/PQS2); also elsewhere on the board
/QSPI_CS0: U102.20 (QSPI_CS0/SDA/CTS1/PQS3); also elsewhere on the board
/QSPI_CS1: U102.19 (QSPI_CS1/PQS4); also elsewhere on the board
/QSPI_CS2: U102.13 (QSPI_CS2/PQS5); also elsewhere on the board
/QSPI_CS3: U102.12 (QSPI_CS3/SYNCA/SYNCB/PQS6); also elsewhere on the board
/QSPI_DIN: U102.16 (QSPI_DIN/EZPD/CANRX/RXD1/PQS1); also elsewhere on the board
/RCON-: R112.1, U102.21 (RCON/EZPCS); also elsewhere on the board
/RSTI-: BDM_PORT101.7, D102.2 (A), R106.2, U102.96 (RSTI); also elsewhere on the board
/RSTO-: R115.1, U102.97 (RSTO); also elsewhere on the board
/TCLK: BDM_PORT101.24 (P20), CLKOUT101.1, CT101.2, R114.2, R117.1
/UCTS0: U102.6 (~UCTS0/CANRX/PUA3); also elsewhere on the board
/UCTS1: U102.98 (~UCTS1/SYNCA/URXD2/PUB3); also elsewhere on the board
/UCTS2: U102.27 (~UCTS2/PUC3); also elsewhere on the board
/URTS0: U102.9 (~URTS0/CANTX/PUA2); also elsewhere on the board
/URTS1: U102.4 (~URTS1/SYNCB/UTXD2/PUB2); also elsewhere on the board
/URTS2: U102.30 (~URTS2/PUC2); also elsewhere on the board
/URXD0: U102.7 (URXD0/PUA1); also elsewhere on the board
/URXD1: U102.100 (URXD1/PUB1); also elsewhere on the board
/URXD2: U102.28 (URXD2/PUC1); also elsewhere on the board
/UTXD0: U102.8 (UTXD0/PUA0); also elsewhere on the board
/UTXD1: U102.99 (UTXD1/PUB0); also elsewhere on the board
/UTXD2: U102.29 (UTXD2/PUC0); also elsewhere on the board
/VCCA: C108.1, C109.1, L102.2, U102.49 (VRH), U102.50 (VCCA); also elsewhere on the board
/VDDPLL: C102.1, C103.1, L101.2, U102.74 (VCCPLL)
/XTAL: C106.1, R125.1, U102.72 (XTAL), Y101.2; also elsewhere on the board
GND: BDM_PORT101.3, BDM_PORT101.5, BDM_PORT101.11, BDM_PORT101.20, BDM_PORT101.23, C101.1, C102.2, C103.2, C104.2, C105.2, C106.2, C107.2, C110.2, C111.2, C112.2, C113.2, C114.2, C115.2, C116.2, C117.2, C118.2, C119.2, FB101.1, GND101.1, JP101.1, JP101.3, JP101.5, LED_RST101.1 (K), LV101.3 (Gbd), R105.2, R113.2, R117.2, RST_SW101.2, U101.3 (GND), U102.3 (GND), U102.15 (GND), U102.24 (GND), U102.25 (GND), U102.35 (GND), U102.42 (GND), U102.56 (GND), U102.67 (GND), U102.71 (GNDPLL), U102.75 (GND), U102.82 (GND), U102.92 (GND); also elsewhere on the board
GNDA: C108.2, C109.2, FB101.2, U102.47 (VSSA), U102.48 (VRL); also elsewhere on the board
unnamed: ABRT_SW101.1, R104.1
unnamed: BDM_PORT101.6, CT101.1
unnamed: BDM_PORT101.26 (P22), TA-101.1
unnamed: C104.1, R104.2, R105.1, U101.2
unnamed: D101.1 (K), R103.2, U101.4
unnamed: C105.1, D102.1 (K), LV101.1 (Rst), RST_SW101.1
unnamed: L102.1, VDDA101.2
unnamed: LEDABRT101.1 (K), R103.1
unnamed: LED_RST101.2 (A), R116.2
unnamed: Q101.2 (B), R115.2
unnamed: Q101.3 (C), R116.1
unnamed: R114.1, U102.64 (TCLK/PSTCLK/CLKOUT)
unnamed: R113.1, U102.5 (TEST)
